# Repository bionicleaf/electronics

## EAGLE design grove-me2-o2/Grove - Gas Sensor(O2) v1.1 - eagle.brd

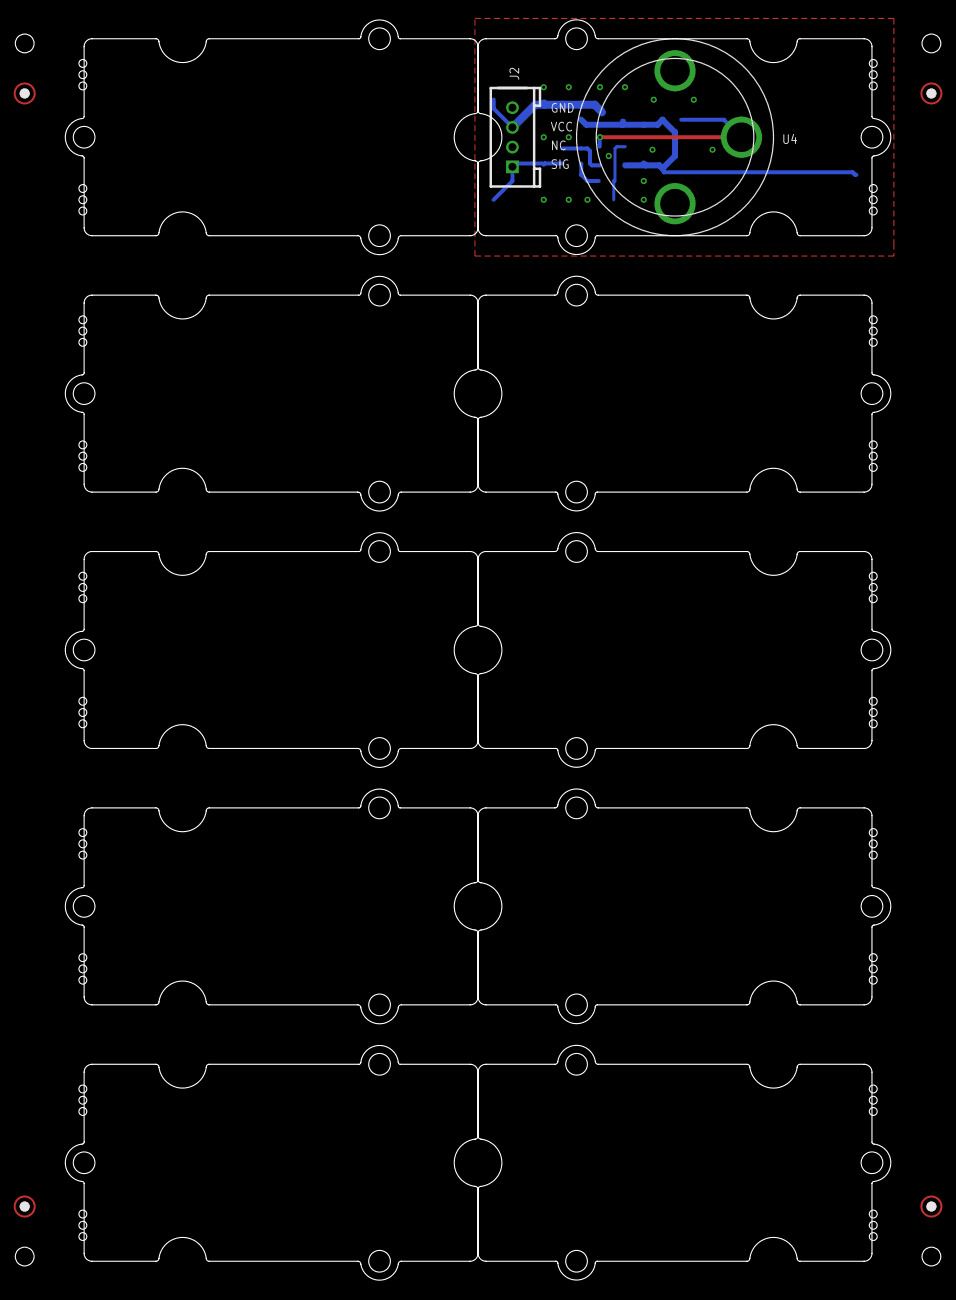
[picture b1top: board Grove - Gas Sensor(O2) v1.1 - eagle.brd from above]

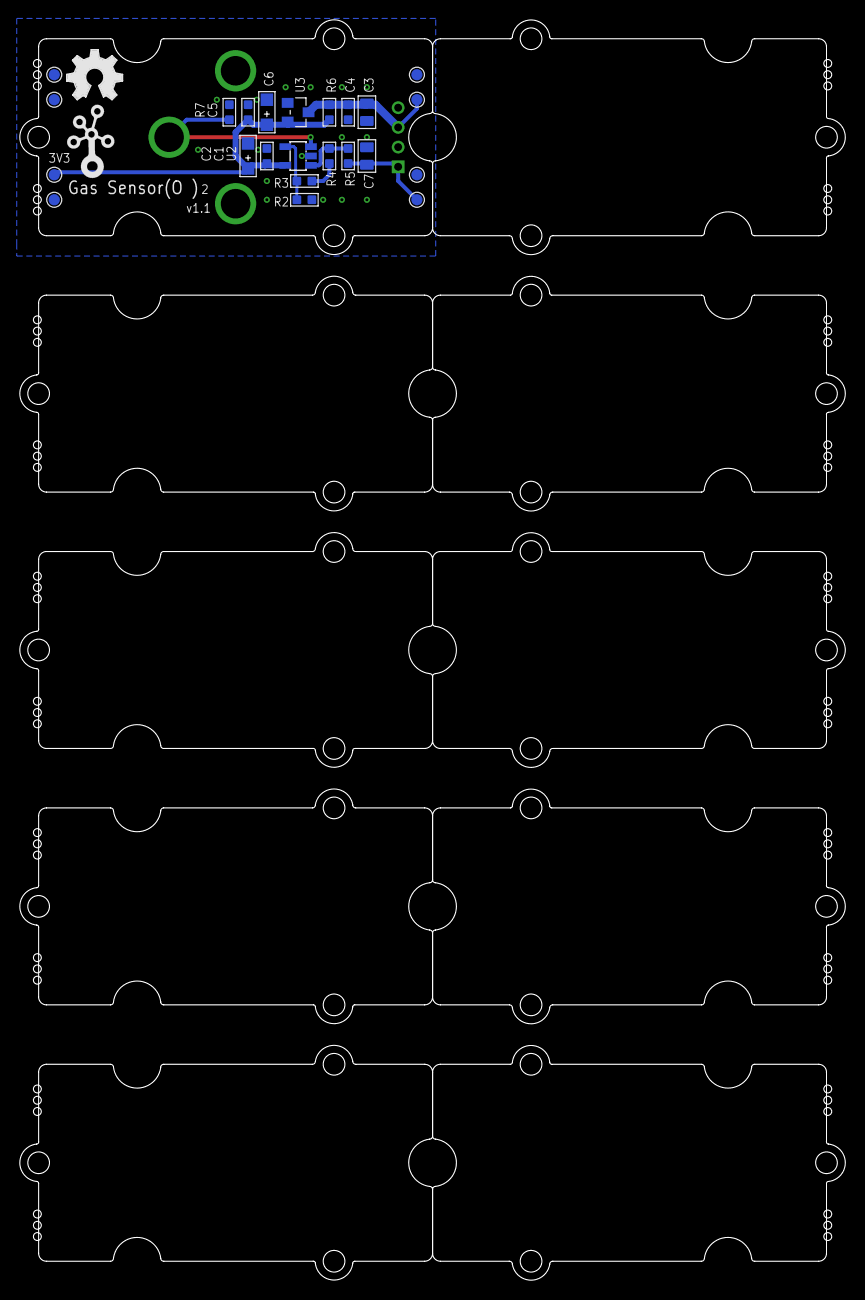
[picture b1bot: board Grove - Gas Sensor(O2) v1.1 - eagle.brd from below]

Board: 2 copper layers, 83.8 x 128.0 mm, 41 parts (25 on the bottom side), 8 nets.

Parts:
C1: 100nF; C0603
C2: 16V_10uF; AVX-A
C3, C7: DNP; C0805
C4, C5: 1uF; C0603
C6: DNP; AVX-A
J2: DIP-Grove; 4P-2.0
P1, P2, P3, P4: ROUND-MARK-1.0
R2, R7: 100R; R0603
R3: 20K; R0603
R4, R5: 0R; R0603
R6: DNP; R0603
TP9, TP10, TP11, TP12, TP13, TP14, TP15, TP16: TP_4545
U2: OPA333DBV; SOT23-5
U3: XC6206332MR; SOT23
U4: ME3-O2; 2P-D20X16H
U$1, U$2, U$3, U$4, U$5, U$6, U$8, U$14, U$16, U$18: GROVE-TEST-PLATFORM
U$15: OSHW_FILLX200_NOTEXT
U$17: TWIGLOGO

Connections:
3V3A: C1.1, C2.+, C5.2, C6.+, R6.1, TP16.T, U2.5, U3.2
GNDA: C1.2, C2.-, C3.1, C4.1, C5.1, C6.-, C7.1, J2.4, R2.1, R7.1, TP10.T, U2.2, U3.1, U4.1
unnamed: R7.2, U2.3, U4.2
unnamed: R2.2, R3.2, U2.4
unnamed: R3.1, R4.2
SIG1A: R4.1, R5.1, U2.1
SIGA: C7.2, J2.1, R5.2, TP12.T
VCCA: C3.2, C4.2, J2.3, R6.2, TP9.T, U3.3

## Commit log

2017-09-29 MQx model
2017-09-29 Added datasheets
2017-09-29 Arduino projects
2017-10-06 Plotting and measuring all the things
2017-11-06 First commit KiCAD project for bionic leaf gas sensor. Non-digital version is implemented in half the schematic. Digital interface is added on the left side of the schematic. Still needs resistor val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
2017-11-07 Schematic passes checks. Nearly complete. Need to sort out alert, addr and cs pins on digital side.
2017-11-07 Tweaks to schematic. Add screen capture: schematic.png
2017-11-07 More tweaks. Find out how to fill background of components, so update bionicleaf.lib and schematic.
2017-11-07 Restore rescue.lib since an error box is generated without it.
2017-11-07 Update screen capture
2017-11-07 Begin PCB layout.
2017-11-10 Minor change to pcb
2017-11-10 Add back headers to separate analog board from digital.
2017-11-11 Add 'PCB Design Reduced EMI.pdf'
2017-11-13 Start adding capacitors and improve PCB layout.
2017-11-15 Autorouted version 1 (gas-sensor-simple.kicad_pcb). Start work on version 2 layout (layout.kicad_pcb) moving RPi connector to top of digital board.
2017-11-15 Updated layout.kicad_pcb with RPi connector moved, routed and cleaned up.
2017-11-15 Version of boards that was sent for prototypes
2017-11-29 Add ground planes. Create new gerbers in layout2.gerbers.
2017-11-29 Adjust board edges.
2017-11-29 Adjust board positions to align common edge.
2017-11-29 Latest and greatest keeping generated gerber file extensions.
2018-01-23 Hotplate Schematic
2018-02-19 Update with additions to hotplate and datasheets.
2018-02-20 Move python code to software directory under gas-sensor-simple.
2018-03-03 Add python project inir_ch4 for methane sensor.
2018-03-04 Minor modifications
2018-03-04 Fix project file which had now defunct win32tests.py in the project.
2018-03-07 Add engr data parser to print ppm and temperature.
2018-03-08 Add methanation documents. Change output to print data on one line.
2018-03-10 Add DBD and associated papers.
2018-03-14 More methanation and plasma papers.
2018-03-23 Add data read support for ZE03-H2 sensor in a python class. Example usage at the end of main.py.
2018-03-24 Rename ZE03_H2 to ZE03 since this code works for ZE03-O2 sensor as well.
2018-03-24 Add support for reading T6615 and add datasheet and user manual for this to datasheets folder.
2018-03-24 Add support in main.py for multiple devices at the same time.
2018-03-25 Debug multi-sensor code.
2018-03-26 Add global port definitions in main.py.
2018-03-28 Bug fixes for inir_ch4-only code. Add logging. Argparser is broken under visual studio for some reason. Need to run program from command prompt for now.
